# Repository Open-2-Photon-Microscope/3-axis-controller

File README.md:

# 3-axis-controller

A manipulator device to operate microscope stage XYZ translations. This project was specifically designed for the OpenFlexure Delta Stage.
  
## Assembly

### Assembling the Board
1. Order the (2 layer) board from a PCB manufacturer (e.g. JLCPCB) by uploading [this file](electronics/integrated_board/Fabrication%20files/integrated_board_gerbers.zip).
1. Using the [BOM](BOM.xlsx), solder together the integrated board from [electronics/integrated_board](electronics/integrated_board). The board is labeled with the locations and values of resistors, capacitors etc.
    * _Make sure to solder socket headers to the board and slot in the esp32 and pcf8575 modules rather than soldering them directly to the board. Sometimes things go wrong and they will be very hard to remove..._
    * _All parts are intended to be soldered as sitting on the top face of the board - any differences seen in the 3D view of the PCB in KiCAD should be ignored_

## Software
### Setting up MicroPython with Thonny IDE
1. Follow the tutorial on [this page](https://randomnerdtutorials.com/getting-started-thonny-micropython-python-ide-esp32-esp8266/) if you haven't already done so when assembling the board.   
### Upload the Code
1. Download the code [here](micropython/)
1. Open them all in Thonny.
    * *Connect your board to your PC via micro USB.*
1. In Thonny, in the files panel (`view > files`) navigate to the location of the code to be installed
1. Highlight all files and folders, including `lib`
1. Right click and select `Upload to /`
1. __CHECK:__ Does the file layout in the esp32 look like that on this GitHub?  

### Assembling the controller
1. Assemble the JST-XH cables mentioned in the BOM
1. For each button and flip switch, cut one crimped wire in half and solder before attaching to the JST-XH head Orientation doesn't matter.  
    
1. Print the [enclosure top](box%20design/enclosure_top.stl) and assemble as shown. Include the other rotary encoders and switches (not shown). The appropriate washers and nuts to screw onto the front face should be shipped with each component. Use M3x10 screws for the LCD.
      
1. Use a 4-pin JST cable to connect the LCD to the marked port. **Make sure** the GND and VCC pins are attached to the same connection on the main and LCD board.
    * _NOTE: there is a variable resistor on the back of the LCD board that adjusts the contrast, so don't screw the whole box shut until you've tested the text appears correctly_  
1. Use a 5-pin JST cable for each rotary encoder. **MAKE SURE** the GND pin connects to the pin marked with "-" on the encoder.
1. Plug in all the switches to the board to their closest port.
    * __DO NOT PLUG SWITCHES INTO THE PORTS MARKED AS 12V/GND AS IT MAY START A FIRE AND SOME FEATURES MAY NOT WORK AS INTENDED__  
1. Once you are confident the LCD is displaying text correctly when powered on, assemble the [enclosure](box%20design/enclosure.stl) as shown. Make sure to print the [feet](box%20design/enclosure_feet.stl) in some TPU for grip. Use M3x16 (or longer).  
 * _Note you should have all components wired up and screwed in at this point, not all of this is shown on the diagram._

### Connecting to the Delta Stage
1. Split the length (2M) of ribbon cable at the ends into 3 strips of 5 wires, and 3 strips of 2 wires. You can peel away the remaining wires and discard them.
    * _Note it may be helpful for cable management not to entirely separate the 3x5 and 3x2 strips._
1. Crimp **one** end of the cable, and slot into JST XH 5 or 2 cable headers respectively.
1. Put a short length of heat-shrink tubing on each remaining end of **all** wires.
1. Next, solder the remaining 3x5 wires to straight JST HX 5 pin headers (male)
    * _Ensure the orientation of both ends of the cable is such that each lane could form a complete loop if it were plugged into itself without any twist. (i.e. each in and out pin is the same)_
1. Solder the sets of 2 wires to the footswitches - one to the middle-pin, the other to the pin towards the hinge of the lever.
    * _Ensure this configuration is such that a circuit is made (not broken) when the switch is pressed_
1. Use hot air or a soldering iron to shrink the heat-shrink tubing and cover these solder joints.
1. Use m2x8 screws to attach the switches to the [modified feet of the Delta Stage](https://github.com/Open-2-Photon-Microscope/OF-larger-delta-stage/blob/main/3D_designs/STL/feet_with_endstop.stl) and use these in place of the ones on the official models when [assembling the actuators](https://build.openflexure.org/openflexure-delta-stage/v1.2.2/pages/index_transmission/pages/assembling_the_actuators.html)
    * Make sure to use the modified models found [here](https://github.com/Open-2-Photon-Microscope/OF-larger-delta-stage/tree/main/3D_designs/STL) for the open 2-photon project  

### Installing the I2C library
#### You may need to install the `lib` portion of the I2C code another way - the above method __should__ work, so only follow these instructions if something is not behaving as expected.
1. Download [micropython-i2c-lcd-0.1.1.tar.gz](https://pypi.org/project/micropython-i2c-lcd/#files)
1. In Thonny go to `Tools > Manage Packages`
    * _make sure the esp32 is still plugged in to your computer_
1. Click the __Install from local file__ link and select the `.tar.gz` file you downloaded
1. __CHECK:__ Does the file layout in the esp32 look like that on this GitHub? You should not need to but you may have to rename the folder to ensure all the code is looking in the right place...

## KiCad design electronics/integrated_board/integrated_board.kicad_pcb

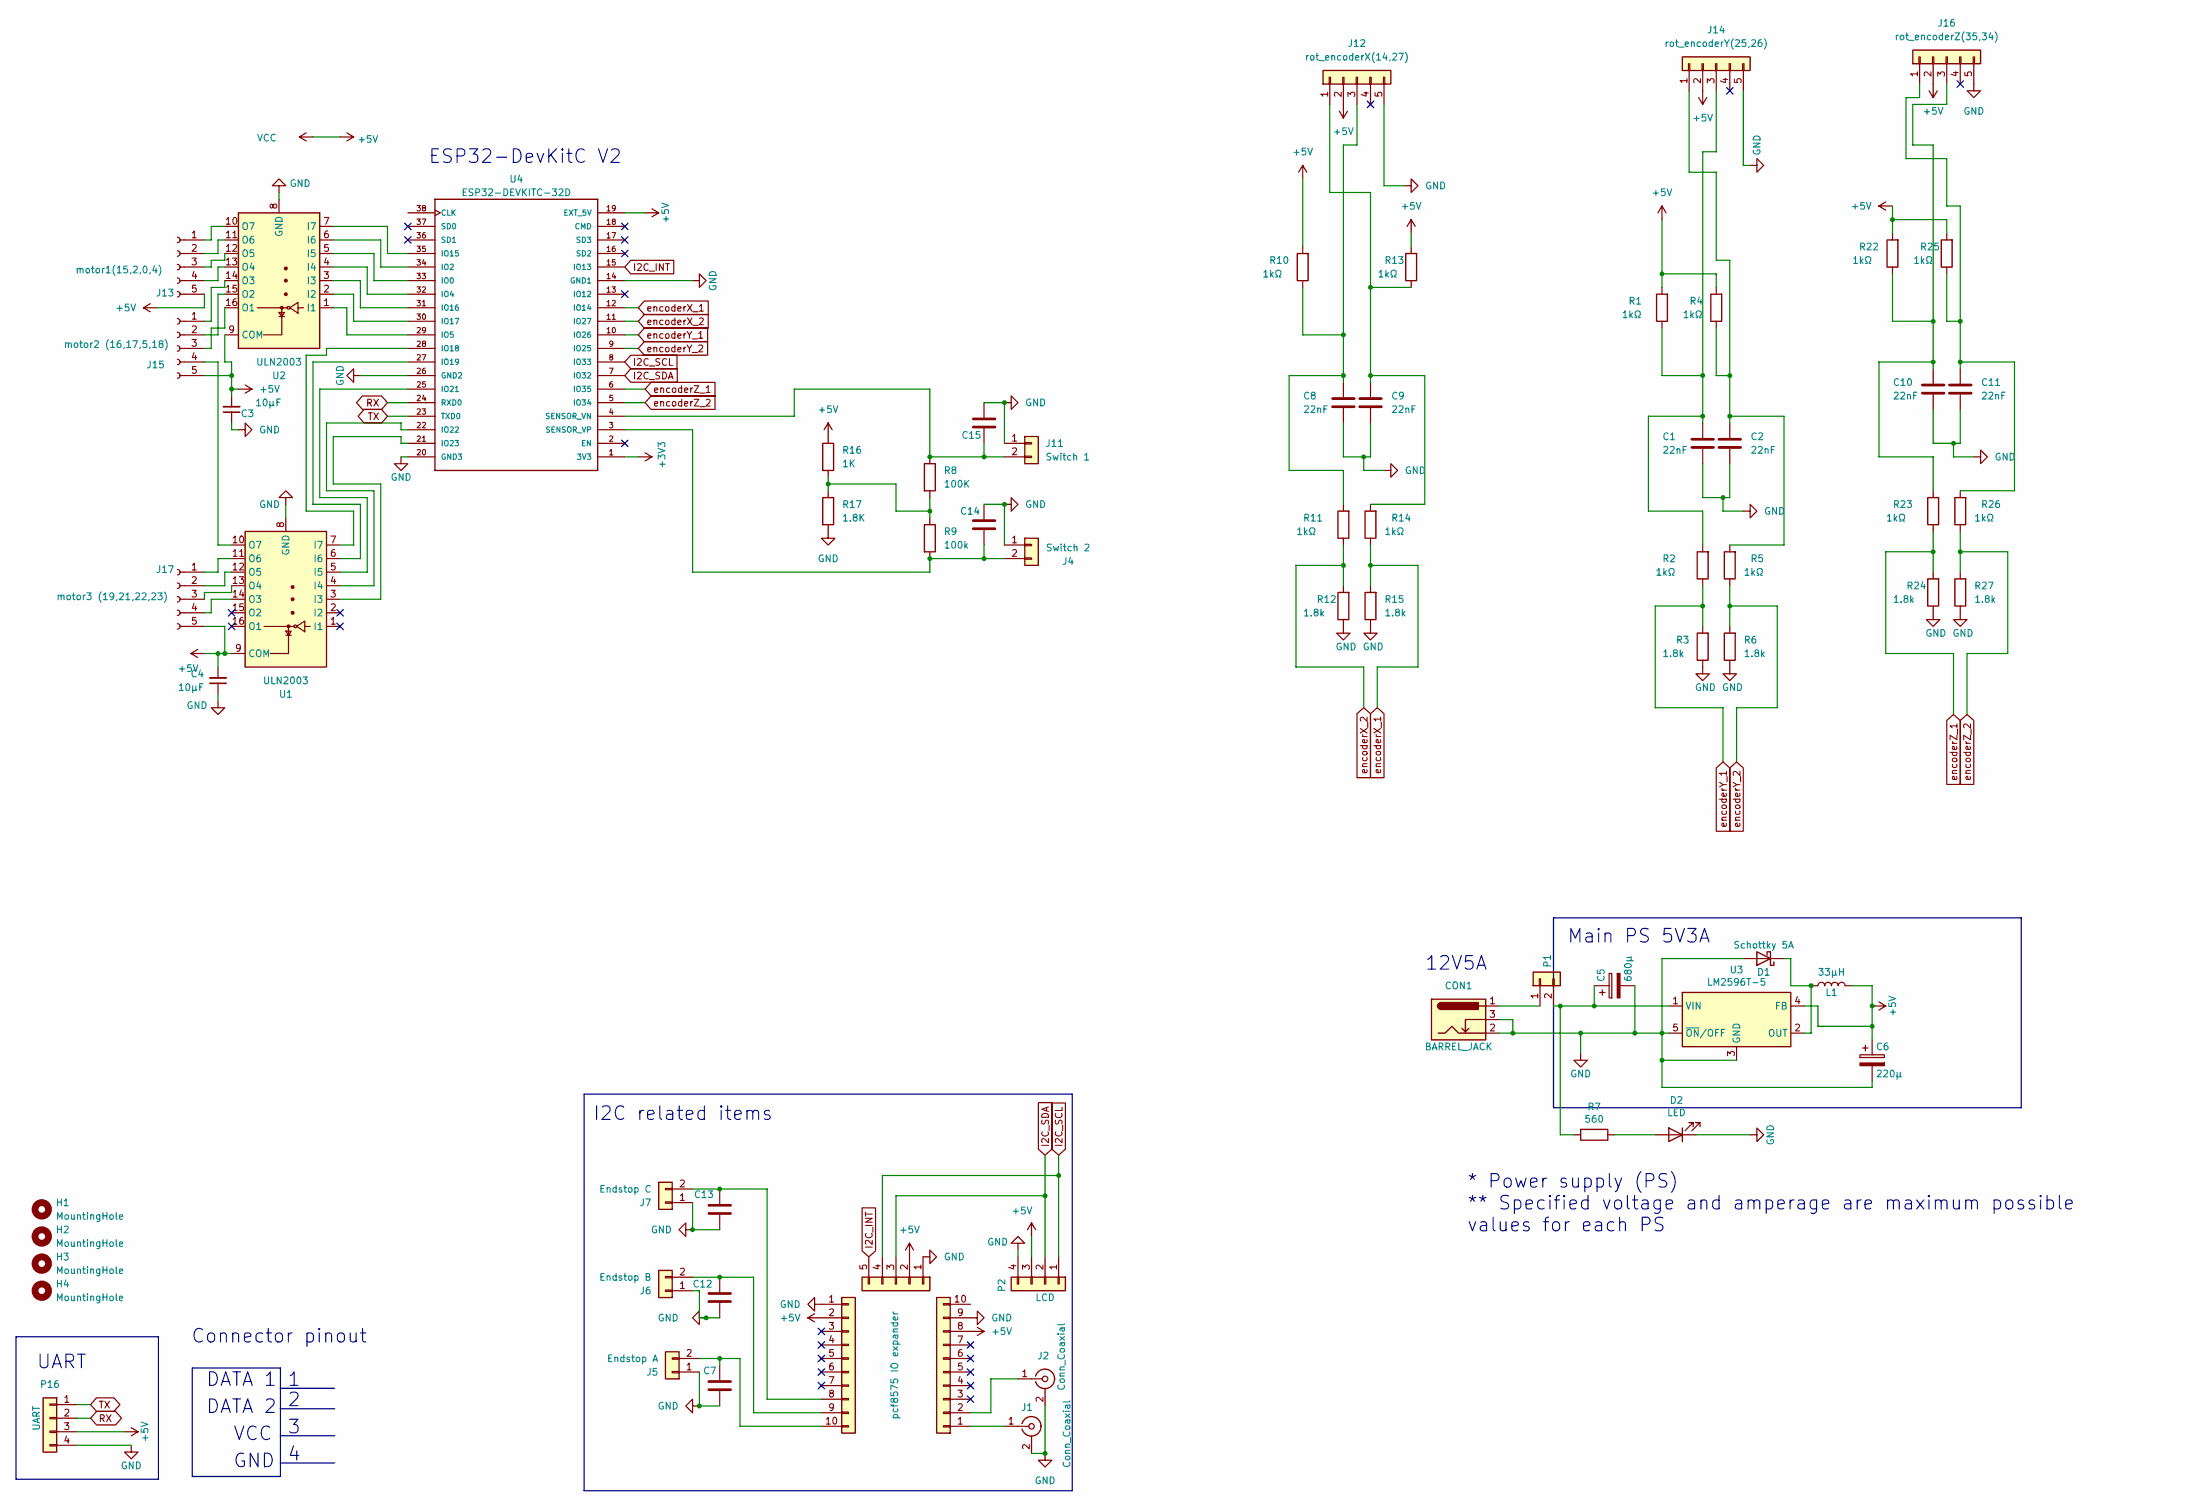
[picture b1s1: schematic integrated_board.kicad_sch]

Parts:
C1, C2, C8, C9, C10, C11: 22nF; C_Disc_D6.0mm_W4.4mm_P5.00mm
C3, C4: 10µF; C_Disc_D6.0mm_W4.4mm_P5.00mm
C5: 680µ; CP_Radial_D10.0mm_P2.50mm_P5.00mm
C6: 220µ; CP_Radial_D8.0mm_P3.80mm
C7, C12, C13, C14, C15: 33nF; C_Disc_D6.0mm_W4.4mm_P5.00mm
CON1: BARREL_JACK; BarrelJack_Horizontal
D1: Schottky 5A; D_DO-201AD_P15.24mm_Horizontal
D2: LED; LED_D3.0mm
H1, H2, H3, H4: MountingHole; MountingHole_3.2mm_M3_DIN965
J1, J2: Conn_Coaxial; BNC_Amphenol_B6252HB-NPP3G-50_Horizontal
J4: Switch 2; JST_XH_B2B-XH-A_1x02_P2.50mm_Vertical
J5: Endstop A; JST_XH_S2B-XH-A_1x02_P2.50mm_Horizontal
J6: Endstop B; JST_XH_S2B-XH-A_1x02_P2.50mm_Horizontal
J7: Endstop C; JST_XH_S2B-XH-A_1x02_P2.50mm_Horizontal
J8, J9: Conn_01x16; PinHeader_1x10_P2.54mm_Vertical
J10: pcf8575 IO expander; PinHeader_1x05_P2.54mm_Vertical
J11: Switch 1; JST_XH_B2B-XH-A_1x02_P2.50mm_Vertical
J12: rot_encoderX(14,27); JST_XH_B5B-XH-A_1x05_P2.50mm_Vertical
J13: motor1(15,2,0,4); JST_XH_S5B-XH-A_1x05_P2.50mm_Horizontal
J14: rot_encoderY(25,26); JST_XH_B5B-XH-A_1x05_P2.50mm_Vertical
J15: motor2 (16,17,5,18); JST_XH_S5B-XH-A_1x05_P2.50mm_Horizontal
J16: rot_encoderZ(35,34); JST_XH_B5B-XH-A_1x05_P2.50mm_Vertical
J17: motor3 (19,21,22,23); JST_XH_S5B-XH-A_1x05_P2.50mm_Horizontal
L1: 33µH; L_Radial_D10.0mm_P5.00mm_Neosid_SD12_style3
P1: Conn_01x02; JST_XH_B2B-XH-A_1x02_P2.50mm_Vertical
P2: LCD; JST_XH_B4B-XH-A_1x04_P2.50mm_Vertical
P16: UART; JST_XH_B4B-XH-A_1x04_P2.50mm_Vertical
R1, R2, R4, R5, R10, R11, R13, R14, R22, R23, R25, R26: 1kΩ; R_Axial_DIN0309_L9.0mm_D3.2mm_P12.70mm_Horizontal
R3, R6, R12, R15, R24, R27: 1.8k; R_Axial_DIN0309_L9.0mm_D3.2mm_P12.70mm_Horizontal
R7: 560; R_Box_L13.0mm_W4.0mm_P9.00mm
R8: 100K; R_Axial_DIN0309_L9.0mm_D3.2mm_P12.70mm_Horizontal
R9: 100k; R_Axial_DIN0309_L9.0mm_D3.2mm_P12.70mm_Horizontal
R16: 1K; R_Axial_DIN0309_L9.0mm_D3.2mm_P12.70mm_Horizontal
R17: 1.8K; R_Axial_DIN0309_L9.0mm_D3.2mm_P12.70mm_Horizontal
U1, U2: ULN2003; DIP-16_W7.62mm_LongPads
U3: LM2596T-5; TO-220-5_P3.4x3.7mm_StaggerOdd_Lead3.8mm_Vertical
U4: ESP32-DEVKITC-32D; MODULE_ESP32-DEVKITC-32D

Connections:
+3V3: U4.1 (3V3)
+5V: C3.2, C4.2, C6.1, J8.8, J9.2, J10.2, J12.2, J13.5, J14.2, J15.5, J16.2, J17.5, L1.2, P2.3, P16.3, R1.2, R4.2, R10.2, R13.2, R16.1, R22.2, R25.2, U1.9 (COM), U2.9 (COM), U3.4 (FB), U4.19 (EXT_5V)
GND: C1.1, C2.1, C3.1, C4.1, C5.2, C6.2, C7.1, C8.1, C9.1, C10.1, C11.1, C12.1, C13.1, C14.1, C15.1, CON1.2, CON1.3, D1.2 (A), D2.1 (K), J1.2 (Ext), J2.2 (Ext), J4.1, J5.1, J6.1, J7.1, J8.9, J9.1, J10.1, J11.1, J12.5, J14.5, J16.5, P2.4, P16.4, R3.1, R6.1, R12.1, R15.1, R17.2, R24.1, R27.1, U1.8 (GND), U2.8 (GND), U3.3 (GND), U3.5 (~ON/OFF), U4.14 (GND1), U4.20 (GND3), U4.26 (GND2)
I2C_INT: J10.5, U4.15 (IO13)
I2C_SCL: J10.4, P2.1, U4.8 (IO33)
I2C_SDA: J10.3, P2.2, U4.7 (IO32)
unnamed: D1.1 (K), L1.1, U3.2 (OUT)
unnamed: D2.2 (A), R7.1
unnamed: C14.2, J4.2, R9.2, U4.3 (SENSOR_VP)
unnamed: C7.2, J5.2, J9.10
unnamed: C12.2, J6.2, J9.9
unnamed: C13.2, J7.2, J9.8
unnamed: C15.2, J11.2, R8.1, U4.4 (SENSOR_VN)
unnamed: C9.2, J12.1, R13.1, R14.2
unnamed: C8.2, J12.3, R10.1, R11.2
unnamed: J13.1, U2.10 (O7)
unnamed: J13.2, U2.11 (O6)
unnamed: J13.3, U2.12 (O5)
unnamed: J13.4, U2.13 (O4)
unnamed: C2.2, J14.1, R4.1, R5.2
unnamed: C1.2, J14.3, R1.1, R2.2
unnamed: J15.1, U2.14 (O3)
unnamed: J15.2, U2.15 (O2)
unnamed: J15.3, U2.16 (O1)
unnamed: J15.4, U1.10 (O7)
unnamed: C11.2, J16.1, R25.1, R26.2
unnamed: C10.2, J16.3, R22.1, R23.2
unnamed: J17.1, U1.11 (O6)
unnamed: J17.2, U1.12 (O5)
unnamed: J17.3, U1.13 (O4)
unnamed: J17.4, U1.14 (O3)
unnamed: CON1.1, P1.1
unnamed: C5.1, P1.2, R7.2, U3.1 (VIN)
unnamed: R8.2, R9.1, R16.2, R17.1
unnamed: U1.3 (I3), U4.21 (IO23)
unnamed: U1.4 (I4), U4.22 (IO22)
unnamed: U1.5 (I5), U4.25 (IO21)
unnamed: U1.6 (I6), U4.27 (IO19)
unnamed: U1.7 (I7), U4.28 (IO18)
unnamed: U2.1 (I1), U4.29 (IO5)
unnamed: U2.2 (I2), U4.30 (IO17)
unnamed: U2.3 (I3), U4.31 (IO16)
unnamed: U2.4 (I4), U4.32 (IO4)
unnamed: U2.5 (I5), U4.33 (IO0)
unnamed: U2.6 (I6), U4.34 (IO2)
unnamed: U2.7 (I7), U4.35 (IO15)
RX: P16.2, U4.24 (RXD0)
TX: P16.1, U4.23 (TXD0)
encoderX_1: R14.1, R15.2, U4.12 (IO14)
encoderX_2: R11.1, R12.2, U4.11 (IO27)
encoderY_1: R2.1, R3.2, U4.10 (IO26)
encoderY_2: R5.1, R6.2, U4.9 (IO25)
encoderZ_1: R23.1, R24.2, U4.6 (IO35)
encoderZ_2: R26.1, R27.2, U4.5 (IO34)

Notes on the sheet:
I2C related items
DATA 2
UART
Main PS 5V3A
12V5A
Connector pinout
DATA 1
GND
* Power supply (PS) ** Specified voltage and amperage are maximum possible values for each PS
VCC
ESP32-DevKitC V2

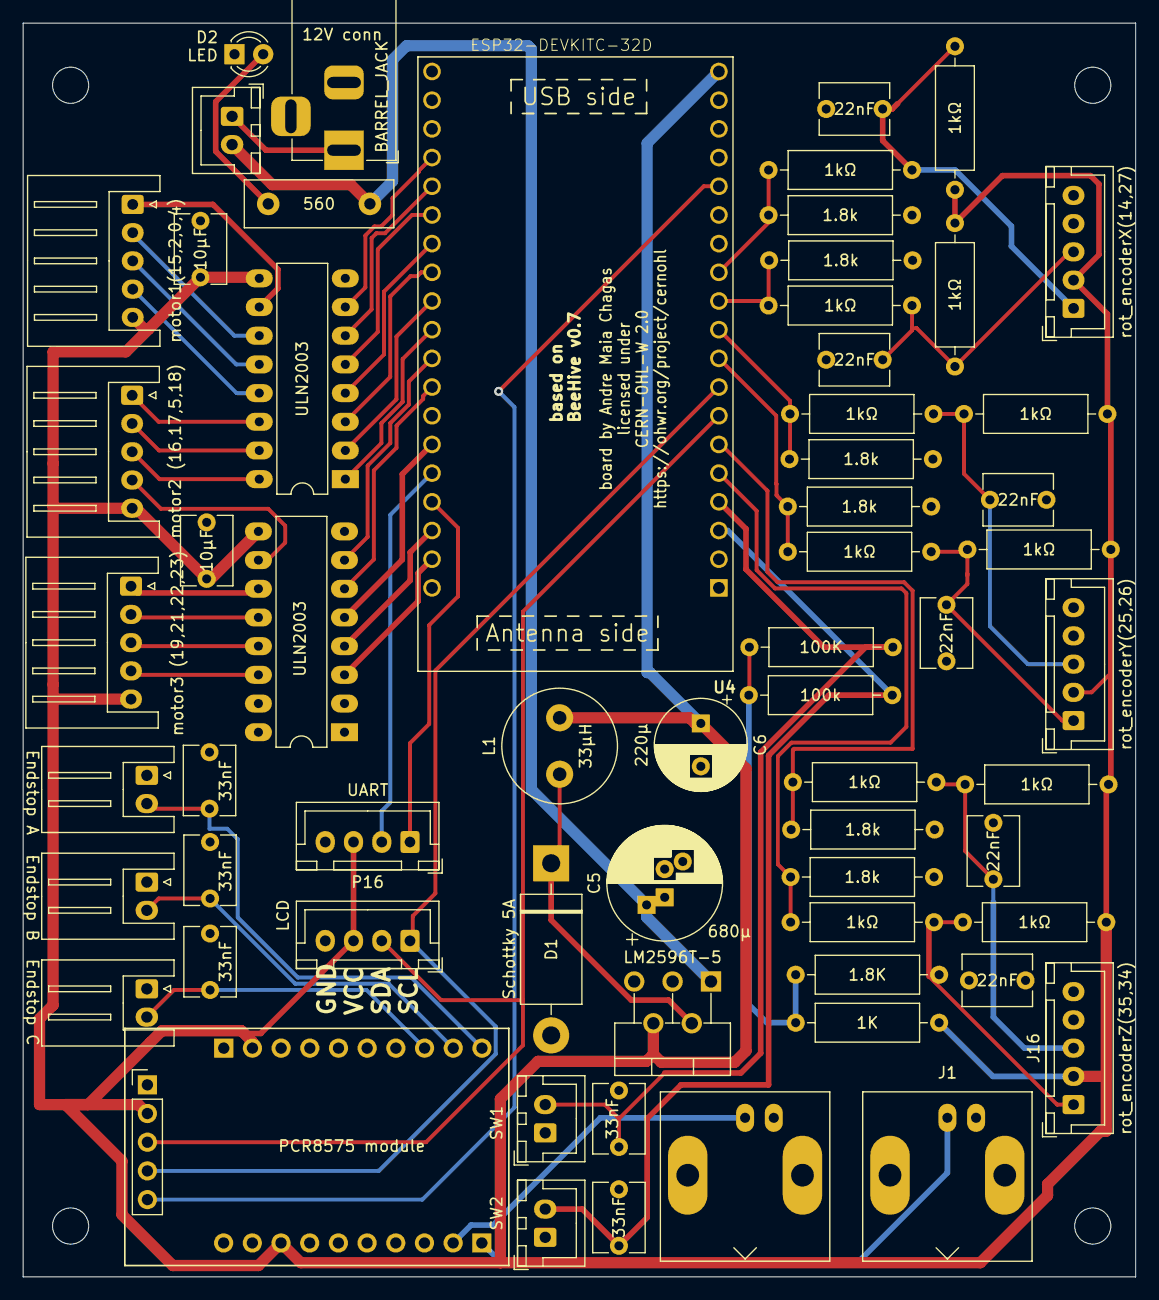
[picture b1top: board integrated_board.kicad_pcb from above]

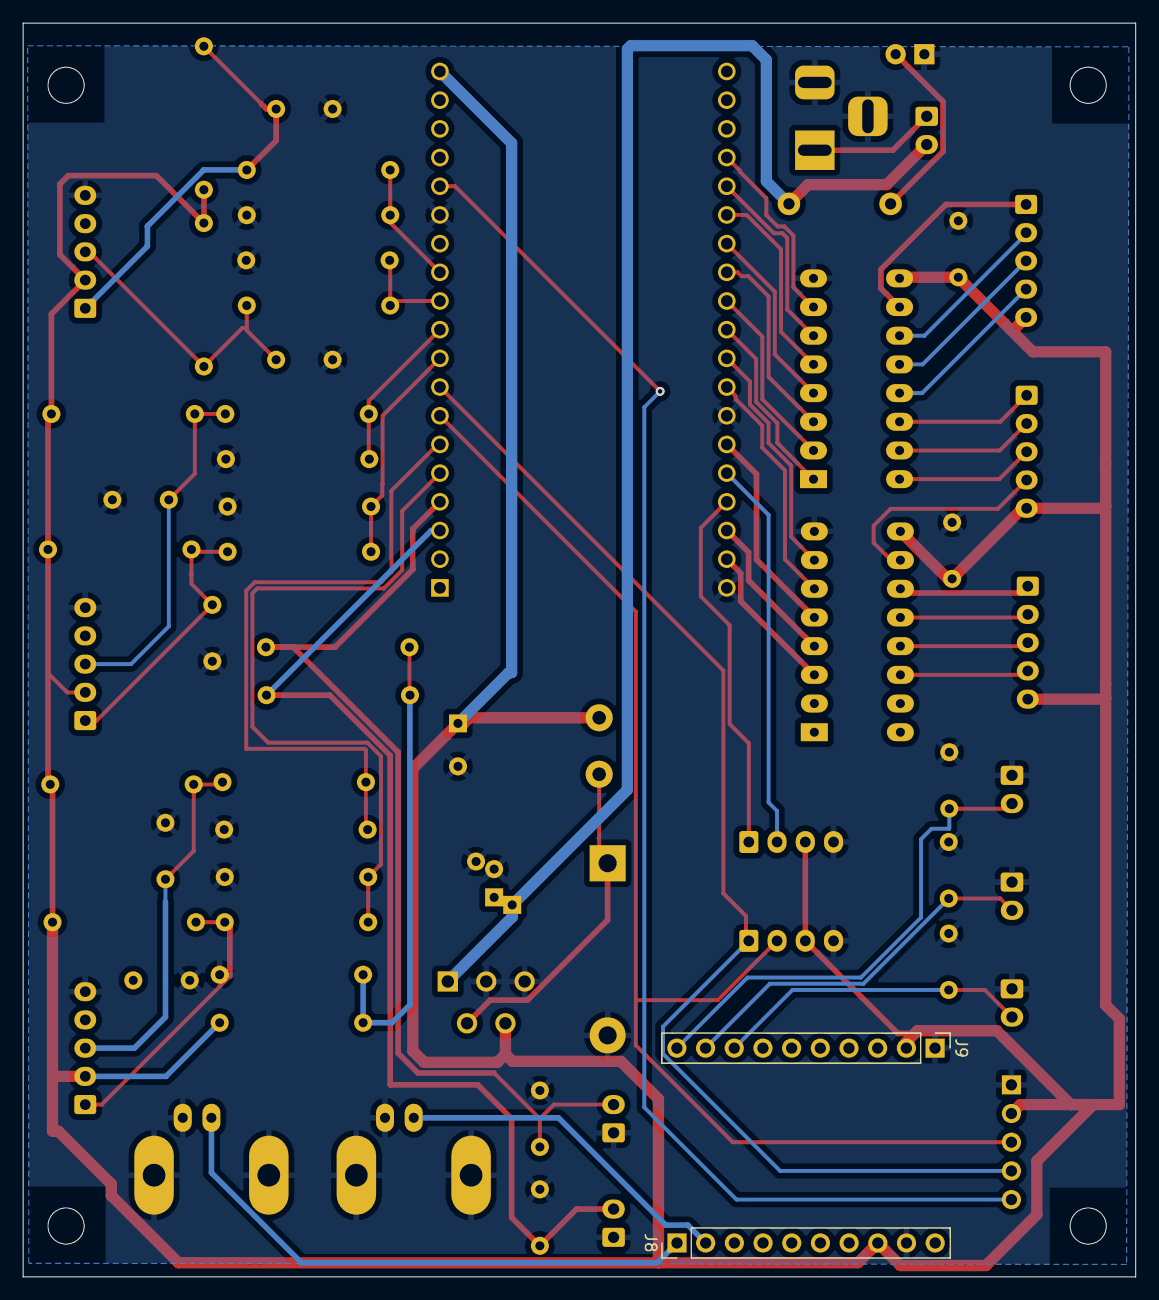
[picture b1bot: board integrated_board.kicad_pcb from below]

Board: 2 copper layers, 98.5 x 111.0 mm, 69 parts (2 on the bottom side), 53 nets.

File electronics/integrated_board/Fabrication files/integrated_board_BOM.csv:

"Id";"Designator";"Footprint";"Quantity";"Designation";"Supplier and ref";
1;"J1";"JST_XH_B4B-XH-A_1x04_P2.50mm_Vertical";1;"rot_encoderZ(35,34)";;;
2;"J6";"JST_XH_S2B-XH-A_1x02_P2.50mm_Horizontal";1;"Endstop B";;;
3;"P1,P10,P15";"JST_XH_B2B-XH-A_1x02_P2.50mm_Vertical";3;"Conn_01x02";;;
4;"R3,R24,R15,R12,R6,R27";"R_Axial_DIN0309_L9.0mm_D3.2mm_P12.70mm_Horizontal";6;"1.8k";;;
5;"R7";"R_Box_L13.0mm_W4.0mm_P9.00mm";1;"560";;;
6;"H3,H2,H1,H4";"MountingHole_3.2mm_M3_DIN965";4;"MountingHole";;;
7;"J4";"JST_XH_B2B-XH-A_1x02_P2.50mm_Vertical";1;"Switch 2";;;
8;"R4,R23,R25,R13,R2,R1,R5,R14,R10,R26,R11,R22";"R_Axial_DIN0309_L9.0mm_D3.2mm_P12.70mm_Horizontal";12;"1kΩ";;;
9;"J11";"JST_XH_B2B-XH-A_1x02_P2.50mm_Vertical";1;"Switch 1";;;
10;"C9,C8,C11,C1,C2,C10";"C_Disc_D6.0mm_W4.4mm_P5.00mm";6;"22nF";;;
11;"C3,C4";"C_Disc_D6.0mm_W4.4mm_P5.00mm";2;"10µF";;;
12;"C12,C7,C14,C15,C13";"C_Disc_D6.0mm_W4.4mm_P5.00mm";5;"C";;;
13;"J13";"JST_XH_S5B-XH-A_1x05_P2.50mm_Horizontal";1;"motor1(15,2,0,4)";;;
14;"P2";"JST_XH_B4B-XH-A_1x04_P2.50mm_Vertical";1;"LCD";;;
15;"U1,U2";"DIP-16_W7.62mm_LongPads";2;"ULN2003";;;
16;"J7";"JST_XH_S2B-XH-A_1x02_P2.50mm_Horizontal";1;"Endstop C";;;
17;"J3";"JST_XH_B4B-XH-A_1x04_P2.50mm_Vertical";1;"rot_encoderX(14,27)";;;
18;"CON1";"BarrelJack_Horizontal";1;"BARREL_JACK";;;
19;"D1";"D_DO-201AD_P15.24mm_Horizontal";1;"Schottky 5A";;;
20;"C5";"CP_Radial_D10.0mm_P2.50mm_P5.00mm";1;"680µ";;;
21;"J2";"JST_XH_B4B-XH-A_1x04_P2.50mm_Vertical";1;"rot_encoderY(25,26)";;;
22;"L1";"L_Radial_D10.0mm_P5.00mm_Neosid_SD12_style3";1;"33µH";;;
23;"U3";"TO-220-5_P3.4x3.7mm_StaggerOdd_Lead3.8mm_Vertical";1;"LM2596T-5";;;
24;"J17";"JST_XH_S5B-XH-A_1x05_P2.50mm_Horizontal";1;"motor3 (19,21,22,23)";;;
25;"D2";"LED_D3.0mm";1;"LED";;;
26;"J15";"JST_XH_S5B-XH-A_1x05_P2.50mm_Horizontal";1;"motor2 (16,17,5,18)";;;
27;"C6";"CP_Radial_D8.0mm_P3.80mm";1;"220µ";;;
28;"J5";"JST_XH_S2B-XH-A_1x02_P2.50mm_Horizontal";1;"Endstop A";;;
29;"J10";"PinHeader_1x05_P2.54mm_Vertical";1;"pcf8575 IO expander";;;
30;"J8,J9";"PinHeader_1x08_P2.54mm_Vertical";2;"Conn_01x16";;;
31;"U4";"MODULE_ESP32-DEVKITC-32D";1;"ESP32-DEVKITC-32D";;;

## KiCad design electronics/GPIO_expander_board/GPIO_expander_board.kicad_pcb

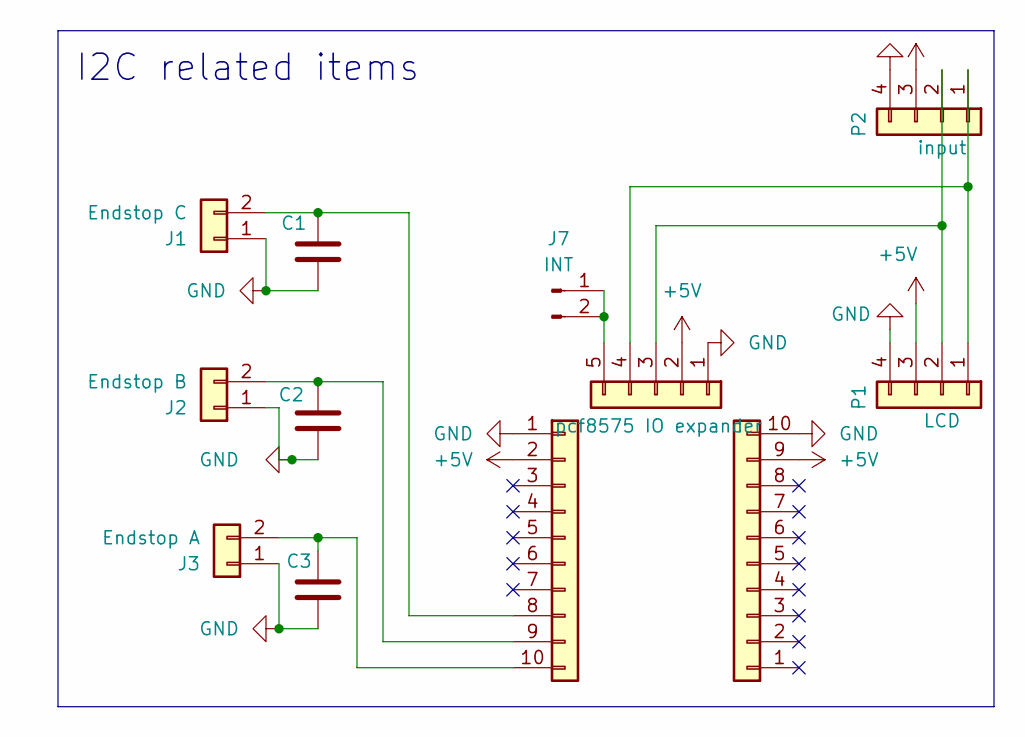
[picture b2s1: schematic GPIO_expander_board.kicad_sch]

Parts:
C1, C2, C3: 33nF; C_Disc_D6.0mm_W4.4mm_P5.00mm
J1: Endstop C; JST_XH_S2B-XH-A_1x02_P2.50mm_Horizontal
J2: Endstop B; JST_XH_S2B-XH-A_1x02_P2.50mm_Horizontal
J3: Endstop A; JST_XH_S2B-XH-A_1x02_P2.50mm_Horizontal
J4, J6: Conn_01x16; PinHeader_1x10_P2.54mm_Vertical
J5: pcf8575 IO expander; PinHeader_1x05_P2.54mm_Vertical
J7: INT; PinHeader_1x02_P2.54mm_Vertical
P1: LCD; JST_XH_B4B-XH-A_1x04_P2.50mm_Vertical
P2: input; JST_XH_B4B-XH-A_1x04_P2.50mm_Vertical

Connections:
+5V: J4.2, J5.2, J6.9, P1.3, P2.3
GND: C1.1, C2.1, C3.1, J1.1, J2.1, J3.1, J4.1, J5.1, J6.10, P1.4, P2.4
unnamed: C1.2, J1.2, J4.8
unnamed: C2.2, J2.2, J4.9
unnamed: C3.2, J3.2, J4.10
unnamed: J5.3, P1.2, P2.2
unnamed: J5.4, P1.1, P2.1
unnamed: J5.5, J7.1, J7.2

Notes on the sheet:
I2C related items

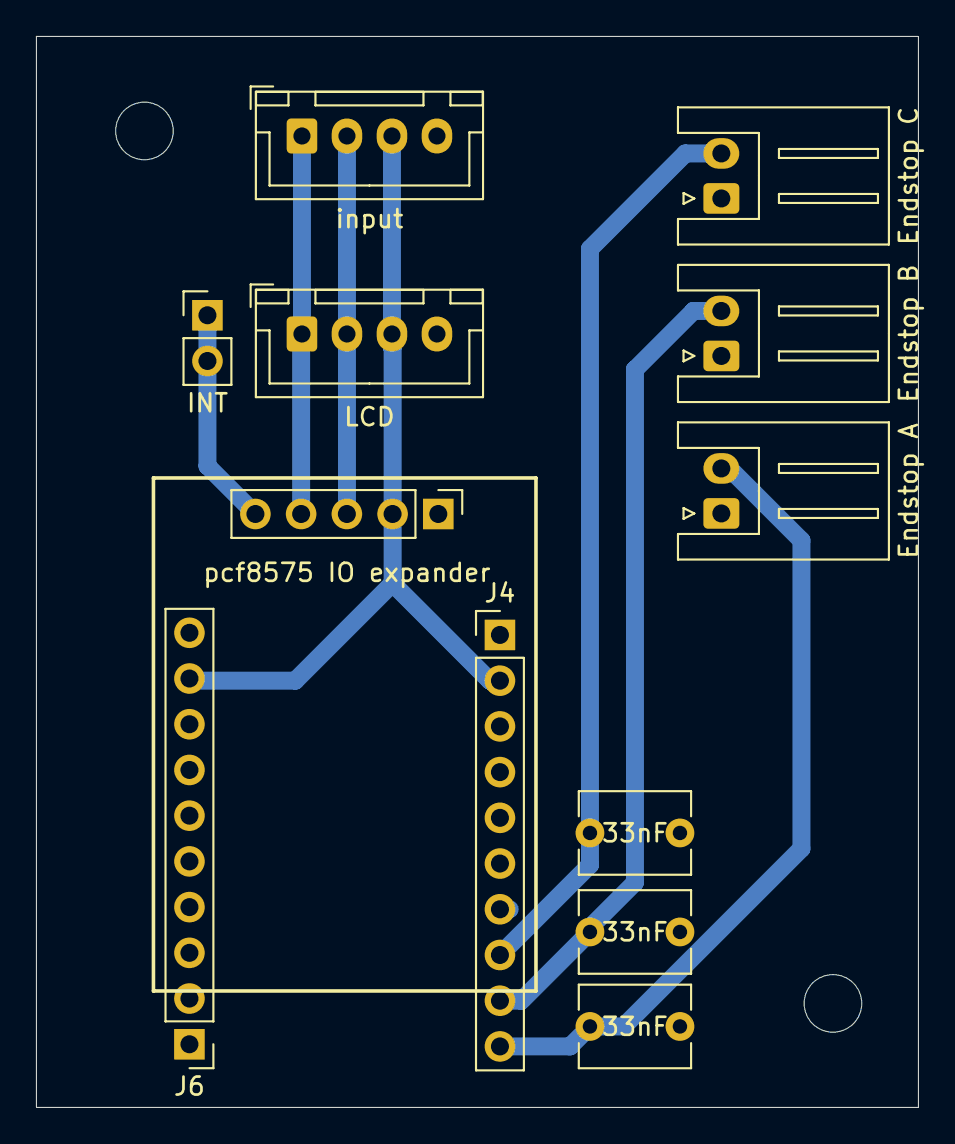
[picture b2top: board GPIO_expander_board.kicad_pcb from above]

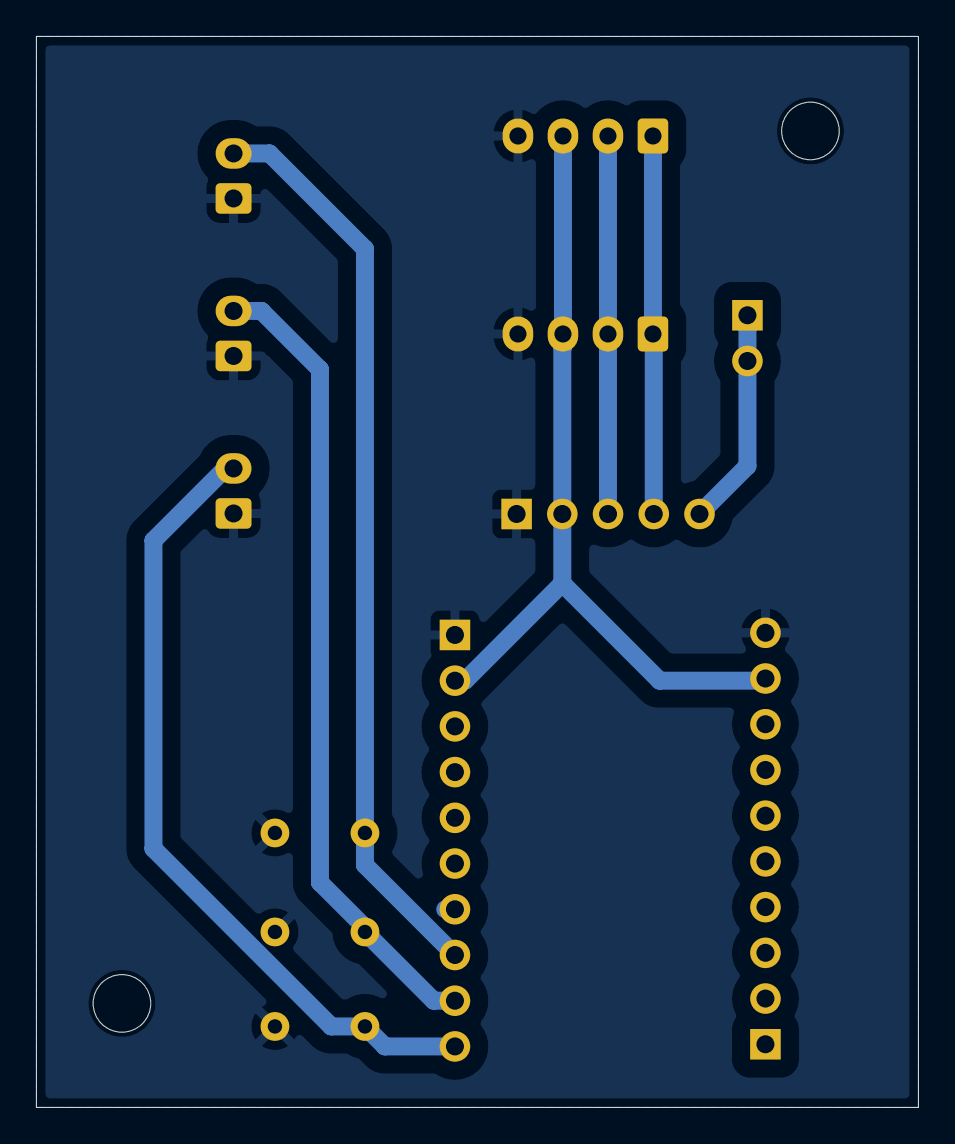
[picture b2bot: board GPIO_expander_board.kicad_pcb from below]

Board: 2 copper layers, 49.0 x 59.5 mm, 14 parts (2 on the bottom side), 8 nets.

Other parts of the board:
H4, H4#2: MountingHole; MountingHole_3.2mm_M3_DIN965

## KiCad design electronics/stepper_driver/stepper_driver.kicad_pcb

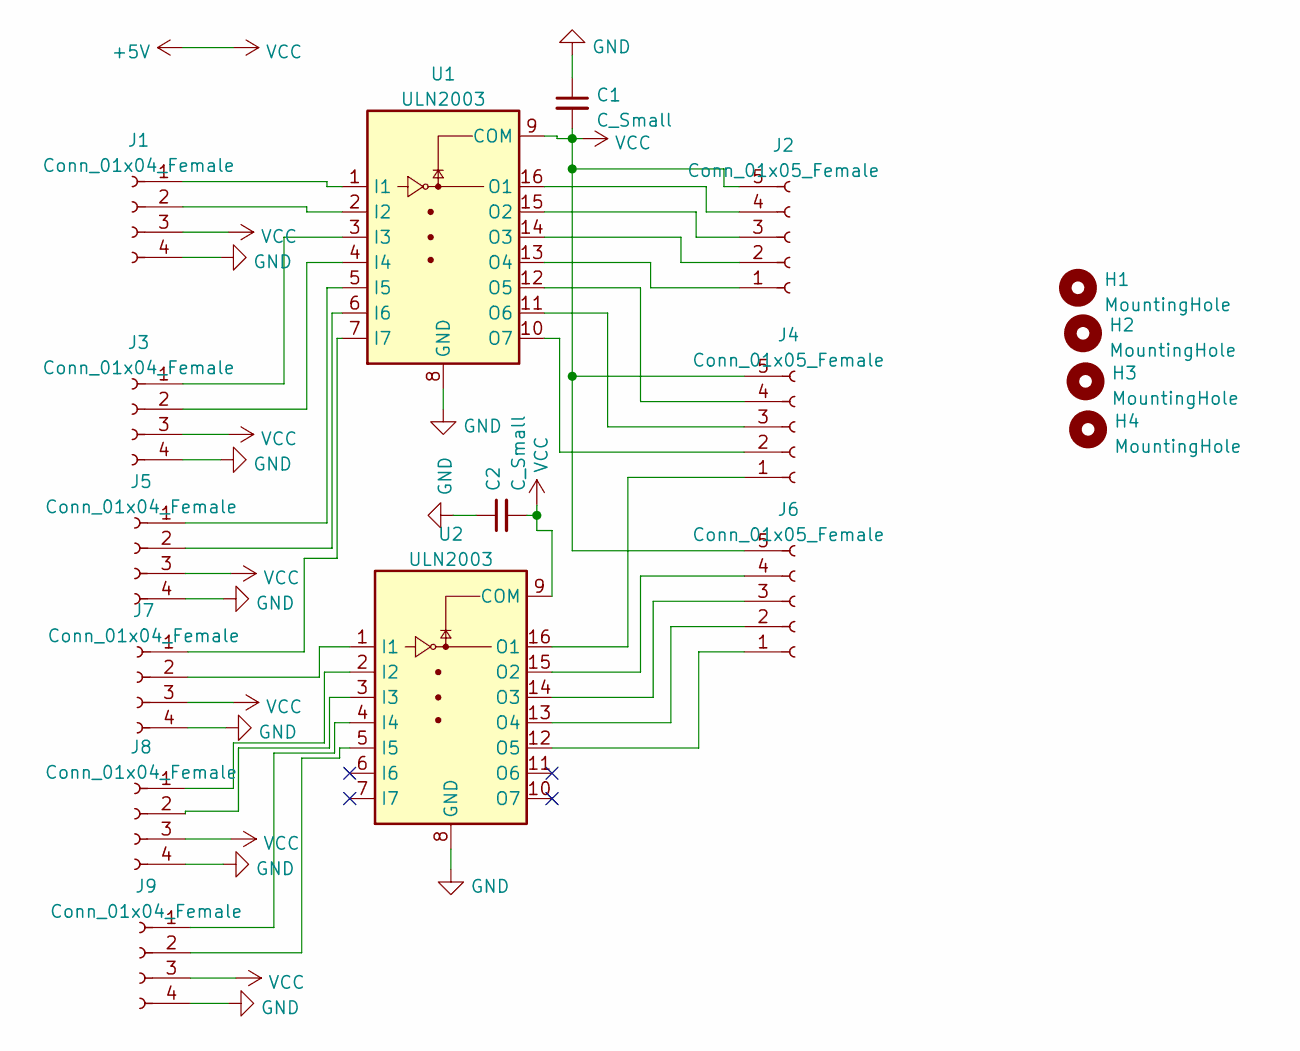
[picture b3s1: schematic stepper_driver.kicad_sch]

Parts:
C1, C2: C_Small; C_Disc_D6.0mm_W4.4mm_P5.00mm
H1, H2, H3, H4: MountingHole; MountingHole_3.2mm_M3
J1, J3, J5, J7, J8, J9: Conn_01x04_Female; JST_XH_S4B-XH-A-1_1x04_P2.50mm_Horizontal
J2, J4, J6: Conn_01x05_Female; JST_XH_S5B-XH-A_1x05_P2.50mm_Horizontal
U1, U2: ULN2003; DIP-16_W7.62mm_Socket_LongPads

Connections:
+5V: C1.2, C2.2, J1.3, J2.5, J3.3, J4.5, J5.3, J6.5, J7.3, J8.3, J9.3, U1.9 (COM), U2.9 (COM)
GND: C1.1, C2.1, J1.4, J3.4, J5.4, J7.4, J8.4, J9.4, U1.8 (GND), U2.8 (GND)
unnamed: J1.1, U1.1 (I1)
unnamed: J1.2, U1.2 (I2)
unnamed: J2.1, U1.13 (O4)
unnamed: J2.2, U1.14 (O3)
unnamed: J2.3, U1.15 (O2)
unnamed: J2.4, U1.16 (O1)
unnamed: J3.1, U1.3 (I3)
unnamed: J3.2, U1.4 (I4)
unnamed: J4.1, U2.16 (O1)
unnamed: J4.2, U1.10 (O7)
unnamed: J4.3, U1.11 (O6)
unnamed: J4.4, U1.12 (O5)
unnamed: J5.1, U1.5 (I5)
unnamed: J5.2, U1.6 (I6)
unnamed: J6.1, U2.12 (O5)
unnamed: J6.2, U2.13 (O4)
unnamed: J6.3, U2.14 (O3)
unnamed: J6.4, U2.15 (O2)
unnamed: J7.1, U1.7 (I7)
unnamed: J7.2, U2.1 (I1)
unnamed: J8.1, U2.2 (I2)
unnamed: J8.2, U2.3 (I3)
unnamed: J9.1, U2.4 (I4)
unnamed: J9.2, U2.5 (I5)

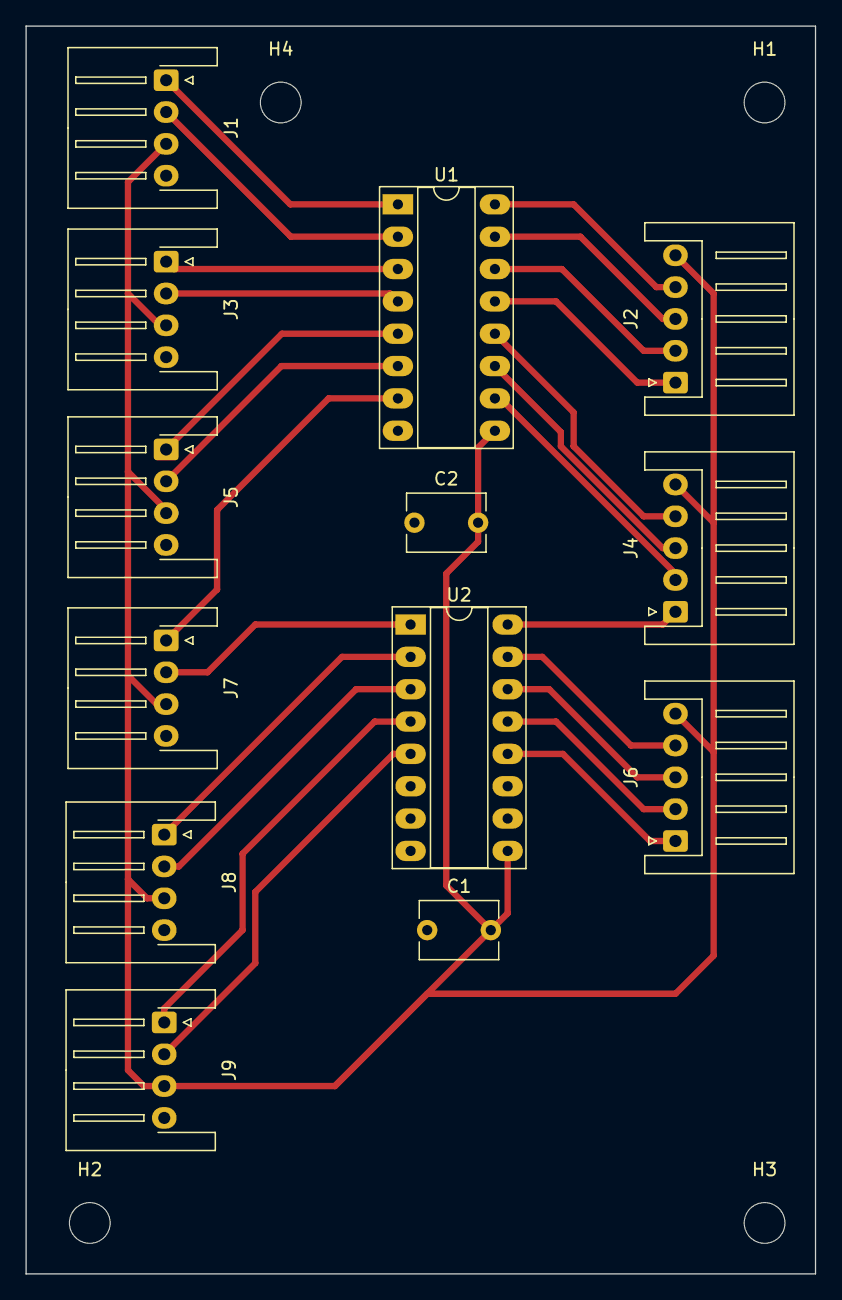
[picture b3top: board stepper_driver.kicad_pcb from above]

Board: 2 copper layers, 62.0 x 98.0 mm, 17 parts (0 on the bottom side), 26 nets.

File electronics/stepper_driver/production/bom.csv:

Designator,Footprint,Quantity,Value,LCSC Part #
J2,JST_XH_S5B-XH-A_1x05_P2.50mm_Horizontal,1,Conn_01x05_Female,
H1,MountingHole_3.2mm_M3,1,MountingHole,
J6,JST_XH_S5B-XH-A_1x05_P2.50mm_Horizontal,1,Conn_01x05_Female,
U2,DIP-16_W7.62mm_Socket_LongPads,1,ULN2003,
C2,C_Disc_D6.0mm_W4.4mm_P5.00mm,1,C_Small,
U1,DIP-16_W7.62mm_Socket_LongPads,1,ULN2003,
J3,JST_XH_S4B-XH-A-1_1x04_P2.50mm_Horizontal,1,Conn_01x04_Female,
H3,MountingHole_3.2mm_M3,1,MountingHole,
J4,JST_XH_S5B-XH-A_1x05_P2.50mm_Horizontal,1,Conn_01x05_Female,
J8,JST_XH_S4B-XH-A-1_1x04_P2.50mm_Horizontal,1,Conn_01x04_Female,
J1,JST_XH_S4B-XH-A-1_1x04_P2.50mm_Horizontal,1,Conn_01x04_Female,
J5,JST_XH_S4B-XH-A-1_1x04_P2.50mm_Horizontal,1,Conn_01x04_Female,
H2,MountingHole_3.2mm_M3,1,MountingHole,
C1,C_Disc_D6.0mm_W4.4mm_P5.00mm,1,C_Small,
J9,JST_XH_S4B-XH-A-1_1x04_P2.50mm_Horizontal,1,Conn_01x04_Female,
H4,MountingHole_3.2mm_M3,1,MountingHole,
J7,JST_XH_S4B-XH-A-1_1x04_P2.50mm_Horizontal,1,Conn_01x04_Female,

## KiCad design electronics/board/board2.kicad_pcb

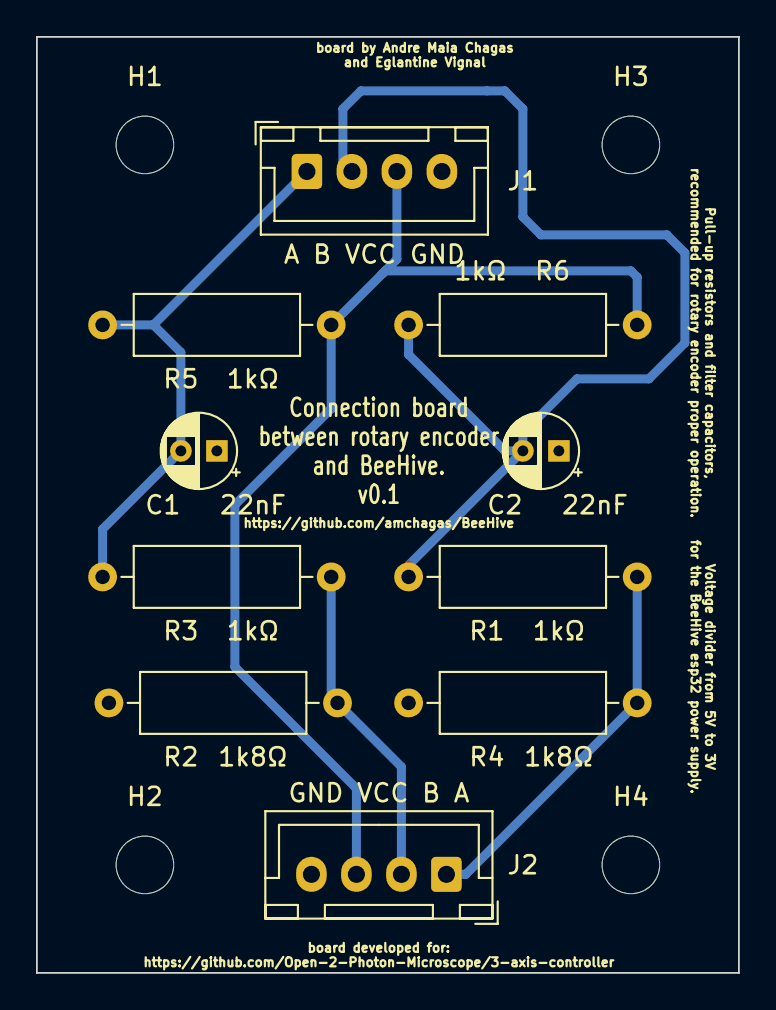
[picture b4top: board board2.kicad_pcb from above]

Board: 2 copper layers, 39.0 x 52.0 mm, 14 parts (0 on the bottom side), 6 nets.

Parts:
C1, C2: 22nF; CP_Radial_D4.0mm_P2.00mm
H1, H2, H3, H4: MountingHole; MountingHole_3.2mm_M3_DIN965
J1: A B VCC GND; JST_XH_B4B-XH-A_1x04_P2.50mm_Vertical
J2: GND VCC B A; JST_XH_B4B-XH-A_1x04_P2.50mm_Vertical
R1, R3, R5, R6: 1kΩ; R_Axial_DIN0309_L9.0mm_D3.2mm_P12.70mm_Horizontal
R2, R4: 1k8Ω; R_Axial_DIN0309_L9.0mm_D3.2mm_P12.70mm_Horizontal

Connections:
+5V: J1.3, J2.3, R5.2, R6.2
GND: C1.1, C2.1, J1.4, J2.4, R2.1, R4.1
unnamed: C1.2, J1.1, R3.2, R5.1
unnamed: C2.2, J1.2, R1.2, R6.1
unnamed: J2.1, R1.1, R4.2
unnamed: J2.2, R2.2, R3.1

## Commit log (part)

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2022-06-28 frame parts
    started to work on freecad to generate the frame for the manipulator
2022-06-28 connection schematics
2022-06-29 dump a bunch of new files
2022-08-17 v0.1 pcb
2022-09-05 Create Developer_guide.md
    Developer guide
2022-09-05 pics
2022-09-05 pics update
2022-09-06 Rename Builder guide.mkd to Builder Guide.md
2022-09-06 common errors
2022-09-06 Rename Developer_guide.md to Common_errors.md
2022-09-09 Rename Builder_guide.md to readme.md
2023-03-27 create drover board and update some code
2023-04-21 fix major board failure
2023-06-08 update issue with board. clean code
2023-11-10 Fixed controller and added user input command
2023-12-05 update and create boards to streamline production
2023-12-06 remove backup files
2023-12-13 moved ipynb files to legacy.
    All remaining files can be dragged and dropped into esp32 via thonny.
2024-06-07 update integrated board
2024-06-26 introducing better code
    not yet finished.
    Faster + synchronous motor movement.
    More accurate/precise movement and readout** (currently in steps not uM)
    LCD works
    Improved rotary encoder reliability.
    Added start/stop buttons.
2024-07-25 finish revision of integrated pcb board, create production files
2024-07-29 Updating README.md
    Updating micropython code
    V1 to be discontinued shortly
    V2 in still in testing
    Updating documentation for installation and assembly
2024-08-01 documentation
    Tidied and updated documentation
2024-08-02 Optimise for new board
    - Inverted z control after new board seems to invert it.
    - Swapped pins talking to I2C to work with new board
2024-08-02 fix board bugs
2024-08-02 remove temp files
2024-08-05 controller upgrade WIP
    To be merged with controller_v2
    Adds customisation option for moving using the controller i.e. cycling through 0.5 um up to 250um increments. The idea is to make larger movements easier and faster.
2024-08-07 enclosure design
2024-08-11 Added modify step size
    also added feet to enclosure scad for TPU printing
2024-08-14 suspended set_step_size
    set_step_size would induce freezing
2024-08-21 Added live movement
2024-08-22 Updates to live movement
2024-09-04 added enclosure stl files
2024-09-05 added set_pins on boot
    prevents current from causing motor A to become hot before a stepper class is defined
2024-09-20 Update cart_del.py
    better comments formatting
    clarifies positions and commands are in STEPs (ie 0.5 um)
2024-11-12 Skippable step size selection
    Useful for automatic data collection /movement. Does not affect normal behaviour
2025-01-27 Redesign full enclosure
    A nice box to reduce exposed electronics of the project.
2025-02-05 Expanding integrated board
    -Board now incorporates pcr8575 gpio expander
    -removed UART port
2025-02-13 Update PCB
    reintroduced push-switches as controlled by individual pins for better use of interrupts
2025-02-15 Updated PCB
    reintroduced voltage divider for switch 1 and 2 as pull up
2025-02-17 Introduced Endstops
    >Endstops class interrupts motor movement
    >re-addressed live movement
    >reorganised the micropython folder to be drag-and-drop friendly
2025-02-26 modular endstop upgrade board
    added board to include expander module and interface with endstops
2025-02-26 Updated endstop protocol
2025-02-27 Fixed enclosure clash
    previous back-slot prevented alignment of screws by clashing with the JTS XH5 connector for motor A
2025-02-27 Updated controls
    -Updated boot to load and run on startup
    - Both buttons pressed will instantly stop all motors
    - Backlash default value set to 100
2025-02-28 Updated integrated PCB
    - fixed footprint for pcf8575
    - updated footprint for rotary encoder connectors for ease of use
2025-02-28 tidying up autosave files
2025-02-28 update enclosure
    - updated design to avoid clashing footprints in the board / enclosure
    - updated gerbers
    -added some illustration images
    -updated README
2025-02-28 Documentation updated
2025-03-03 Display glitch fix
2025-03-03 Updated BOM
2025-03-04 Updated documentation
2025-05-29 Cleaned up files
    -minor fix to zero method
2025-05-29 Added BNC connectors to board
    Intended as receivers of trigger signal for Z-stack
2025-06-02 Update LICENSE
2025-06-12 Added multiple licenses
    Hardware is CERN OHL 1.2
    Software is GNU General Public v3.0
2025-09-27 Ergonomic controller design
2025-09-27 Added set_backlash() to stage
2025-09-30 enclosure draft optimisation

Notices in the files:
electronics/integrated_board/integrated_board.kicad_pcb:
licensed under
CERN-OHL-W 2.0
